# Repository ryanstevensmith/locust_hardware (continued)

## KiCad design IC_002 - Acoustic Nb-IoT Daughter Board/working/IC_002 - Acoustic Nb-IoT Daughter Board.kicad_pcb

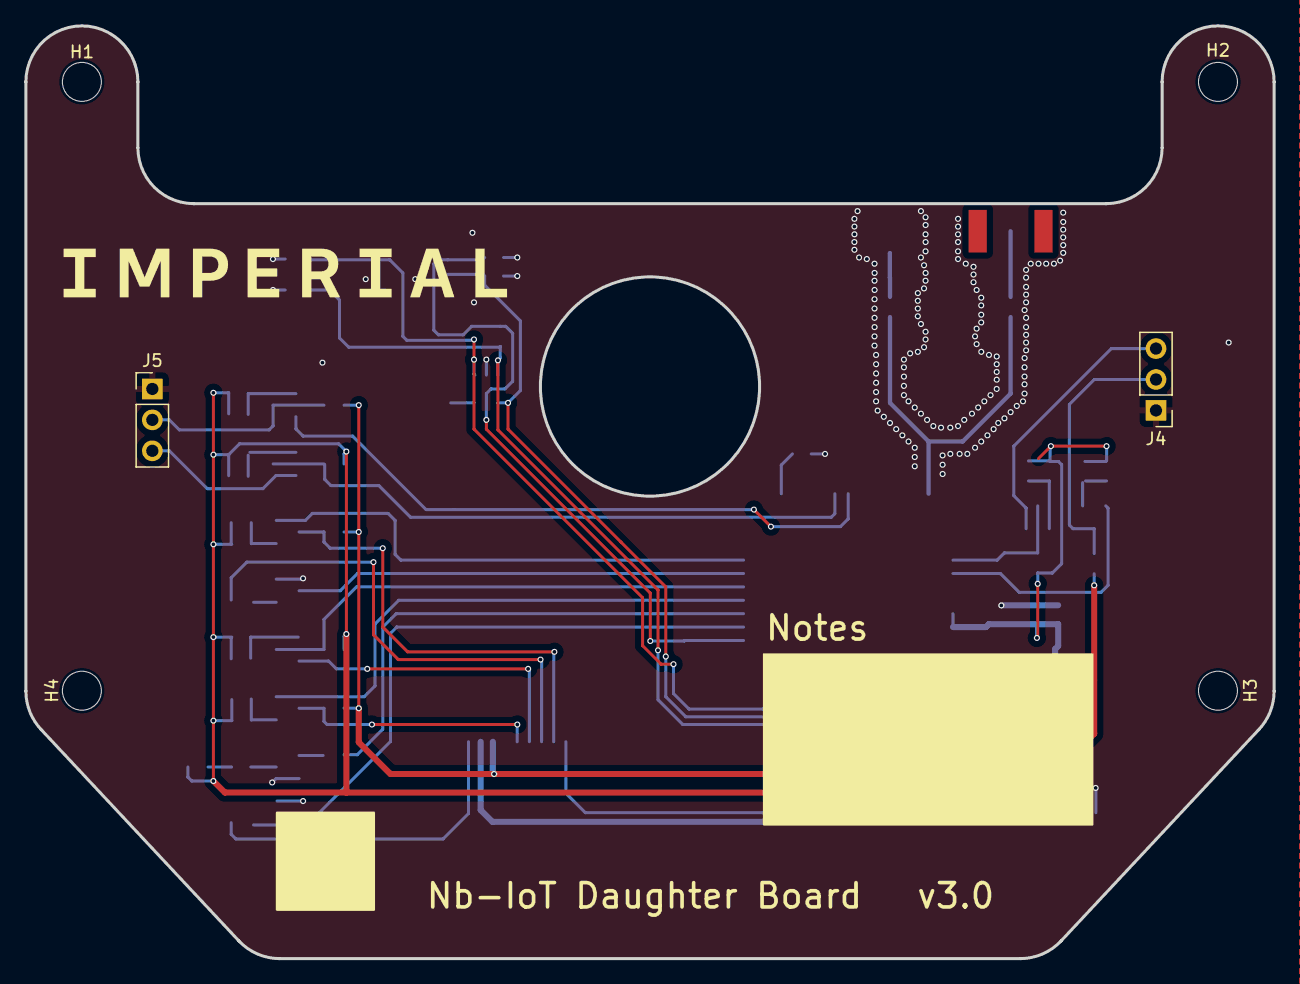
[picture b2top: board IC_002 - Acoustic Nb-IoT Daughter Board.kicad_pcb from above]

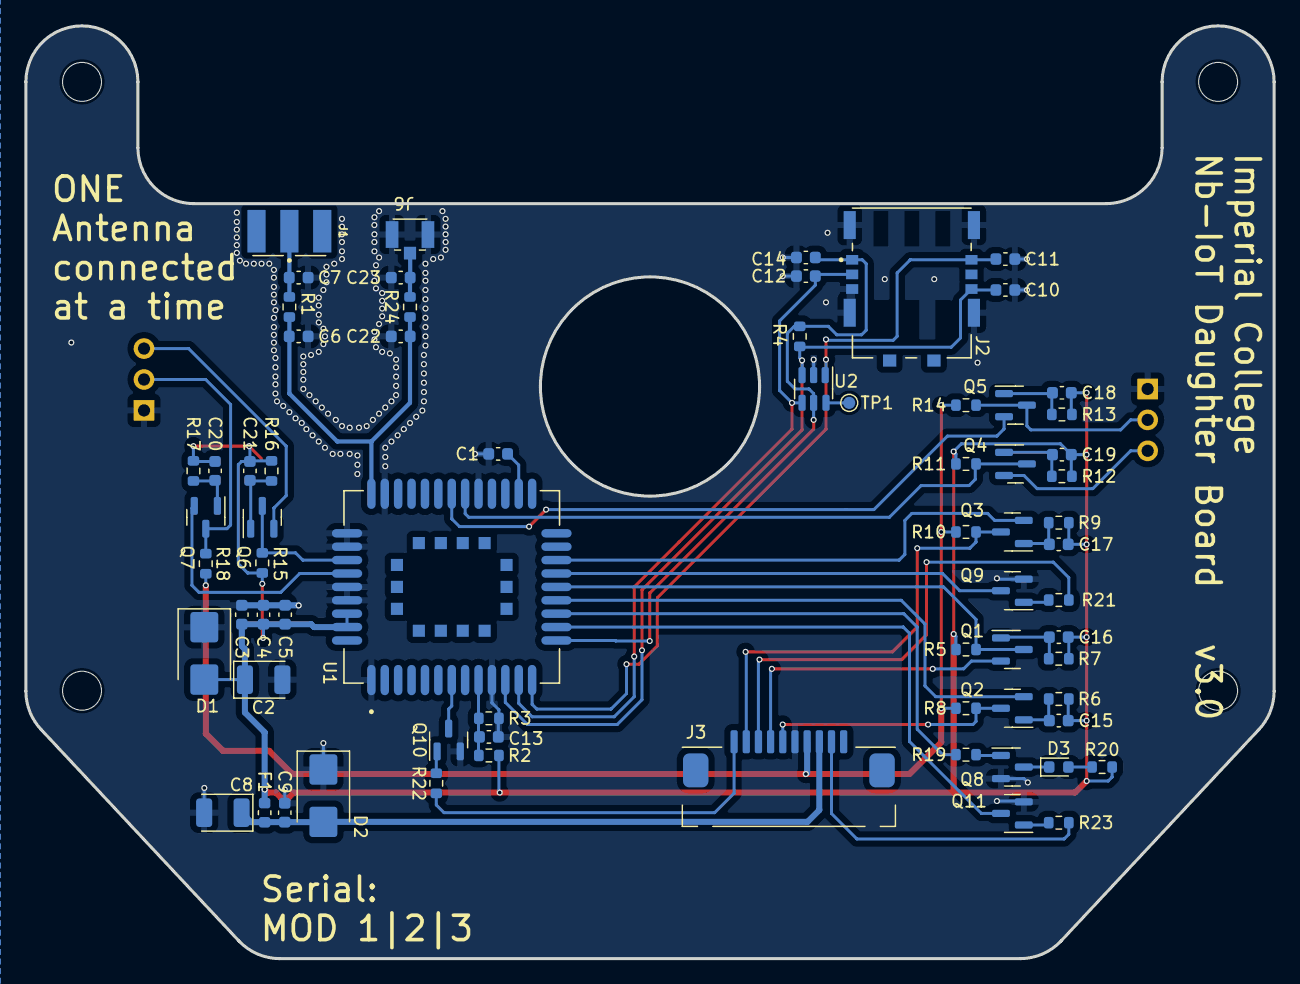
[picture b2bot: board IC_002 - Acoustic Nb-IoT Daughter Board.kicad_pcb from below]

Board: 2 copper layers, 102.5 x 76.6 mm, 75 parts (69 on the bottom side), 48 nets.

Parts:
C1: 2.2uF; C_0603_1608Metric
C2, C8: 100uF; CP_EIA-3528-21_Kemet-B
C3, C9, C13, C14: 100nF; C_0603_1608Metric
C4: 100pF; C_0603_1608Metric
C5, C6, C7, C10, C11, C12, C22, C23: 22pF; C_0603_1608Metric
C15, C16, C17, C18, C19, C20, C21: 1nF; C_0603_1608Metric
D1, D2: P6SMBJ5.0CA; D_SMB
D3: Blue; LED_0603_1608Metric
F1: 1A/32V; Fuse_0603_1608Metric
H1, H2, H3, H4: M3; MountingHole_3.2mm_M3
J1: SMA; CON-SMA-EDGE-S
J2: 104224-0820; MOLEX_104224-0820
J3: 52207-1060
J4, J5: Conn_01x03_Pin; PinHeader_1x03_P2.54mm_Vertical
J6: U.FL; U.FL-R-SMT-1_1
Q1, Q2, Q3, Q4, Q5, Q6, Q7, Q8, Q9, Q10, Q11: BC817; SOT-23
R1, R24: 0R; R_0603_1608Metric
R2: 21K; R_0603_1608Metric
R3, R4, R5, R8, R10, R11, R14, R15, R18: 10K; R_0603_1608Metric
R6, R7, R9, R12, R13, R16, R17: 4K7; R_0603_1608Metric
R19, R20, R21, R22, R23: 1K; R_0603_1608Metric
TP1: TestPoint; TestPoint_Pad_D1.0mm
U1: BC65
U2: SRV05-4HTG-D; TSOT-23-6

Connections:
+3V3: J3.4, R8.2, R10.2, R14.2, R18.2
+3V8: C2.1, C3.1, C4.1, C5.1, C15.2, C16.2, C17.2, C18.2, C19.2, C20.2, C21.2, D1.2 (A2), F1.1, R2.1, R5.1, R6.1, R7.1, R9.1, R11.1, R12.1, R13.1, R15.1, R16.1, R17.1, R20.2, U1.42 (VBAT), U1.43 (VBAT)
/BATT_CONN: C8.1, C9.1, D2.2 (A2), F1.2, J3.3
/BC_ADC: C13.1, R2.2, R3.1, U1.9 (ADC)
/BC_AUX_RXD: Q4.3 (C), R11.2, U1.28 (AUX_RXD)
/BC_AUX_TXD: Q5.2 (E), U1.29 (AUX_TXD)
/BC_DBG_RXD: Q6.3 (C), R15.2, U1.38 (DBG_RXD)
/BC_DBG_TXD: Q7.2 (E), U1.39 (DBG_TXD)
/BC_MAIN_RXD: Q1.3 (C), R5.2, U1.18 (MAIN_RXD)
/BC_MAIN_TXD: Q2.2 (E), U1.17 (MAIN_TXD)
/BC_NETLIGHT: R19.1, U1.16 (NETLIGHT)
/BC_PSM_ENIT: Q9.3 (C), U1.19 (PSM_EINT)
/BC_RI: Q3.2 (E), U1.20 (RI)
/BC_~PWRKEY: Q10.3 (C), U1.7 (~PWRKEY)
/BC_~RESET: Q11.3 (C), U1.15 (~RESET)
/EXT_GPIO1: J3.6, Q2.3 (C), R8.1
/EXT_GPIO2: J3.7, Q1.2 (E)
/EXT_GPIO3: J3.8, R21.1
/EXT_GPIO4: J3.9, Q3.3 (C), R10.1
/EXT_GPIO5: J3.10, R22.1
/EXT_GPIO6: J3.2, R23.1
/USIM_CLK: C11.1, J2.S3 (CLK), U1.13 (USIM_CLK), U2.1 (I/O1)
/USIM_DATA: C10.1, J2.S6 (I/O), R4.2, U1.11 (USIM_DATA), U2.3 (I/O2)
/USIM_RST: C12.1, J2.S2 (RST), U1.12 (USIM_RST), U2.4 (I/O3)
/USIM_VDD: C14.1, J2.S1 (VCC), R4.1, U1.14 (USIM_VDD), U2.5 (VCC)
/VDD_EXT: C1.1, U1.24 (VDD_EXT)
GND: C1.2, C2.2, C3.2, C4.2, C5.2, C6.2, C7.2, C8.2, C9.2, C10.2, C11.2, C12.2, C13.2, C14.2, C22.2, C23.2, D1.1 (A1), D2.1 (A1), J2.G1 (GND), J2.G2 (GND), J2.G3 (GND), J2.G4 (GND), J2.S4 (GND), J3.5, J4.1, J5.1, J6.2 (Ext), Q8.2 (E), Q9.2 (E), Q10.2 (E), Q11.2 (E), R3.2, U1.1 (GND), U1.10 (GND), U1.27 (GND), U1.34 (GND), U1.36 (GND), U1.37 (GND), U1.40 (GND), U1.41 (GND), U2.2 (GND)
unnamed: D3.2 (A), R20.1
unnamed: D3.1 (K), Q8.3 (C)
unnamed: C7.1, J1.1 (In), R1.2
unnamed: J4.2, Q7.3 (C), R18.1
unnamed: J4.3, Q6.2 (E)
unnamed: J5.2, Q5.3 (C), R14.1
unnamed: J5.3, Q4.2 (E)
unnamed: C23.1, J6.1 (In), R24.2
unnamed: C16.1, Q1.1 (B), R7.2
unnamed: C15.1, Q2.1 (B), R6.2
unnamed: C17.1, Q3.1 (B), R9.2
unnamed: C19.1, Q4.1 (B), R12.2
unnamed: C18.1, Q5.1 (B), R13.2
unnamed: C21.1, Q6.1 (B), R16.2
unnamed: C20.1, Q7.1 (B), R17.2
unnamed: Q8.1 (B), R19.2
unnamed: Q9.1 (B), R21.2
unnamed: Q10.1 (B), R22.2
unnamed: Q11.1 (B), R23.2
unnamed: C6.1, C22.1, R1.1, R24.1, U1.35 (ANT_RF)
unnamed: TP1.1, U2.6 (I/O4)

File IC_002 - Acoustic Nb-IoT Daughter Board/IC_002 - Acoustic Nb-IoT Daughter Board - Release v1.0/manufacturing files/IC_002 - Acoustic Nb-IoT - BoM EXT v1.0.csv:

"Source:","IC_002 - Acoustic Nb-IoT Daughter Board.kicad_sch"
"Date:","28/01/2025 16:16:52"
"Tool:","Eeschema 7.0.5"
"Generator:","C:\Program Files\KiCad\7.0\bin\scripting\plugins/bom_csv_grouped_by_value.py"
"Component Count:","66"

"Collated Components:"

"Item","Qty","Reference(s)","Value","LibPart","Footprint","Datasheet","DNP","DigiKey","LCSC","MF","Mouser","PN"
"1","1","C1","2.2uF","Device:C","Capacitor_SMD:C_0603_1608Metric","~","","","","","",""
"2","2","C2, C8","100uF","Device:C_Polarized","Capacitor_Tantalum_SMD:CP_EIA-3528-21_Kemet-B","~","","478-3877-2-ND","","KYOCERA AVX","581-TAJB107M006R","TAJB107M006RNJ"
"3","4","C3, C9, C13, C14","100nF","Device:C","Capacitor_SMD:C_0603_1608Metric","~","","","","","",""
"4","1","C4","100pF","Device:C","Capacitor_SMD:C_0603_1608Metric","~","","","","","",""
"5","4","C5, C10, C11, C12","22pF","Device:C","Capacitor_SMD:C_0603_1608Metric","~","","","","","",""
"6","2","C6, C7","22pF","Device:C","Capacitor_SMD:C_0603_1608Metric","~","DNP","","","","",""
"7","7","C15, C16, C17, C18, C19, C20, C21","1nF","Device:C","Capacitor_SMD:C_0603_1608Metric","~","","","","","",""
"8","2","D1, D2","P6SMBJ5.0CA","Device:D_TVS","Diode_SMD:D_SMB","https://diotec.com/request/datasheet/p6smbj65.pdf","","4878-P6SMBJ5.0CATR-ND","","Diotec","637-P6SMBJ5.0CA","P6SMBJ5.0CA"
"9","1","D3","Blue","Device:LED","LED_SMD:LED_0603_1608Metric","~","","754-1804-2-ND","","Kingbright","604-APTD1608VBCD","APTD1608VBC/D"
"10","1","F1","1A/32V","Device:Polyfuse","Fuse:Fuse_0603_1608Metric","~","","P15124TR-ND","","Panasonic","667-ERB-RE1R00V","P15124TR-ND"
"11","1","J1","SMA","Connector:Conn_Coaxial","SR_Antenna:CON-SMA-EDGE-S"," ~","","CON-SMA-EDGE-S-ND","","RF Solutions","223-CON-SMA-EDGE-S","CON-SMA-EDGE-S"
"12","1","J2","104224-0820","SR_Connectors:104224-0820","SR_Connectors:MOLEX_104224-0820","","","WM23749TR-ND","","Molex","538-104224-0820","104224-0820"
"13","1","J3","52207-1060","Connector_Generic_MountingPin:Conn_01x10_MountingPin","SR_Connectors:52207-1060","~","","WM3753TR-ND","C3168739","Molex","538-52207-1060","52207-1060"
"14","2","J4, J5","Conn_01x03_Pin","Connector:Conn_01x03_Pin","Connector_PinHeader_2.54mm:PinHeader_1x03_P2.54mm_Vertical","~","DNP","-","","-","-","-"
"15","11","Q1, Q2, Q3, Q4, Q5, Q6, Q7, Q8, Q9, Q10, Q11","BC817","Transistor_BJT:BC817","Package_TO_SOT_SMD:SOT-23","https://www.onsemi.com/pub/Collateral/BC818-D.pdf","","1727-BC817-QR-ND","","Nexperia","771-BC817-QR","BC817-QR"
"16","1","R1","0R","Device:R","Resistor_SMD:R_0603_1608Metric","~","","","","","",""
"17","1","R2","21K","Device:R","Resistor_SMD:R_0603_1608Metric","~","","","","","",""
"18","9","R3, R4, R5, R8, R10, R11, R14, R15, R18","10K","Device:R","Resistor_SMD:R_0603_1608Metric","~","","","","","",""
"19","7","R6, R7, R9, R12, R13, R16, R17","4K7","Device:R","Resistor_SMD:R_0603_1608Metric","~","","","","","",""
"20","5","R19, R20, R21, R22, R23","1K","Device:R","Resistor_SMD:R_0603_1608Metric","~","","","","","",""
"21","1","U1","BC65","SR_RF_Module:BC65","SR_RF_Module:BC65","https://www.quectel.com/product/lpwa-bc65-nb-iot/","","2958-BC65PB-04-STDTR-ND","","Quectel","277-BC65PB-04-STD","BC65PB-04-STD"
"22","1","U2","SRV05-4HTG-D","SR_Protection:SRV05-4HTG-D","SR_Package_SOT:TSOT-23-6","https://www.littelfuse.com/assetdocs/littelfuse-tvs-diode-ar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","","SRV05-4HTG-DTR-ND","","LittleFuse","576-SRV05-4HTG-D","SRV05-4HTG-D"
